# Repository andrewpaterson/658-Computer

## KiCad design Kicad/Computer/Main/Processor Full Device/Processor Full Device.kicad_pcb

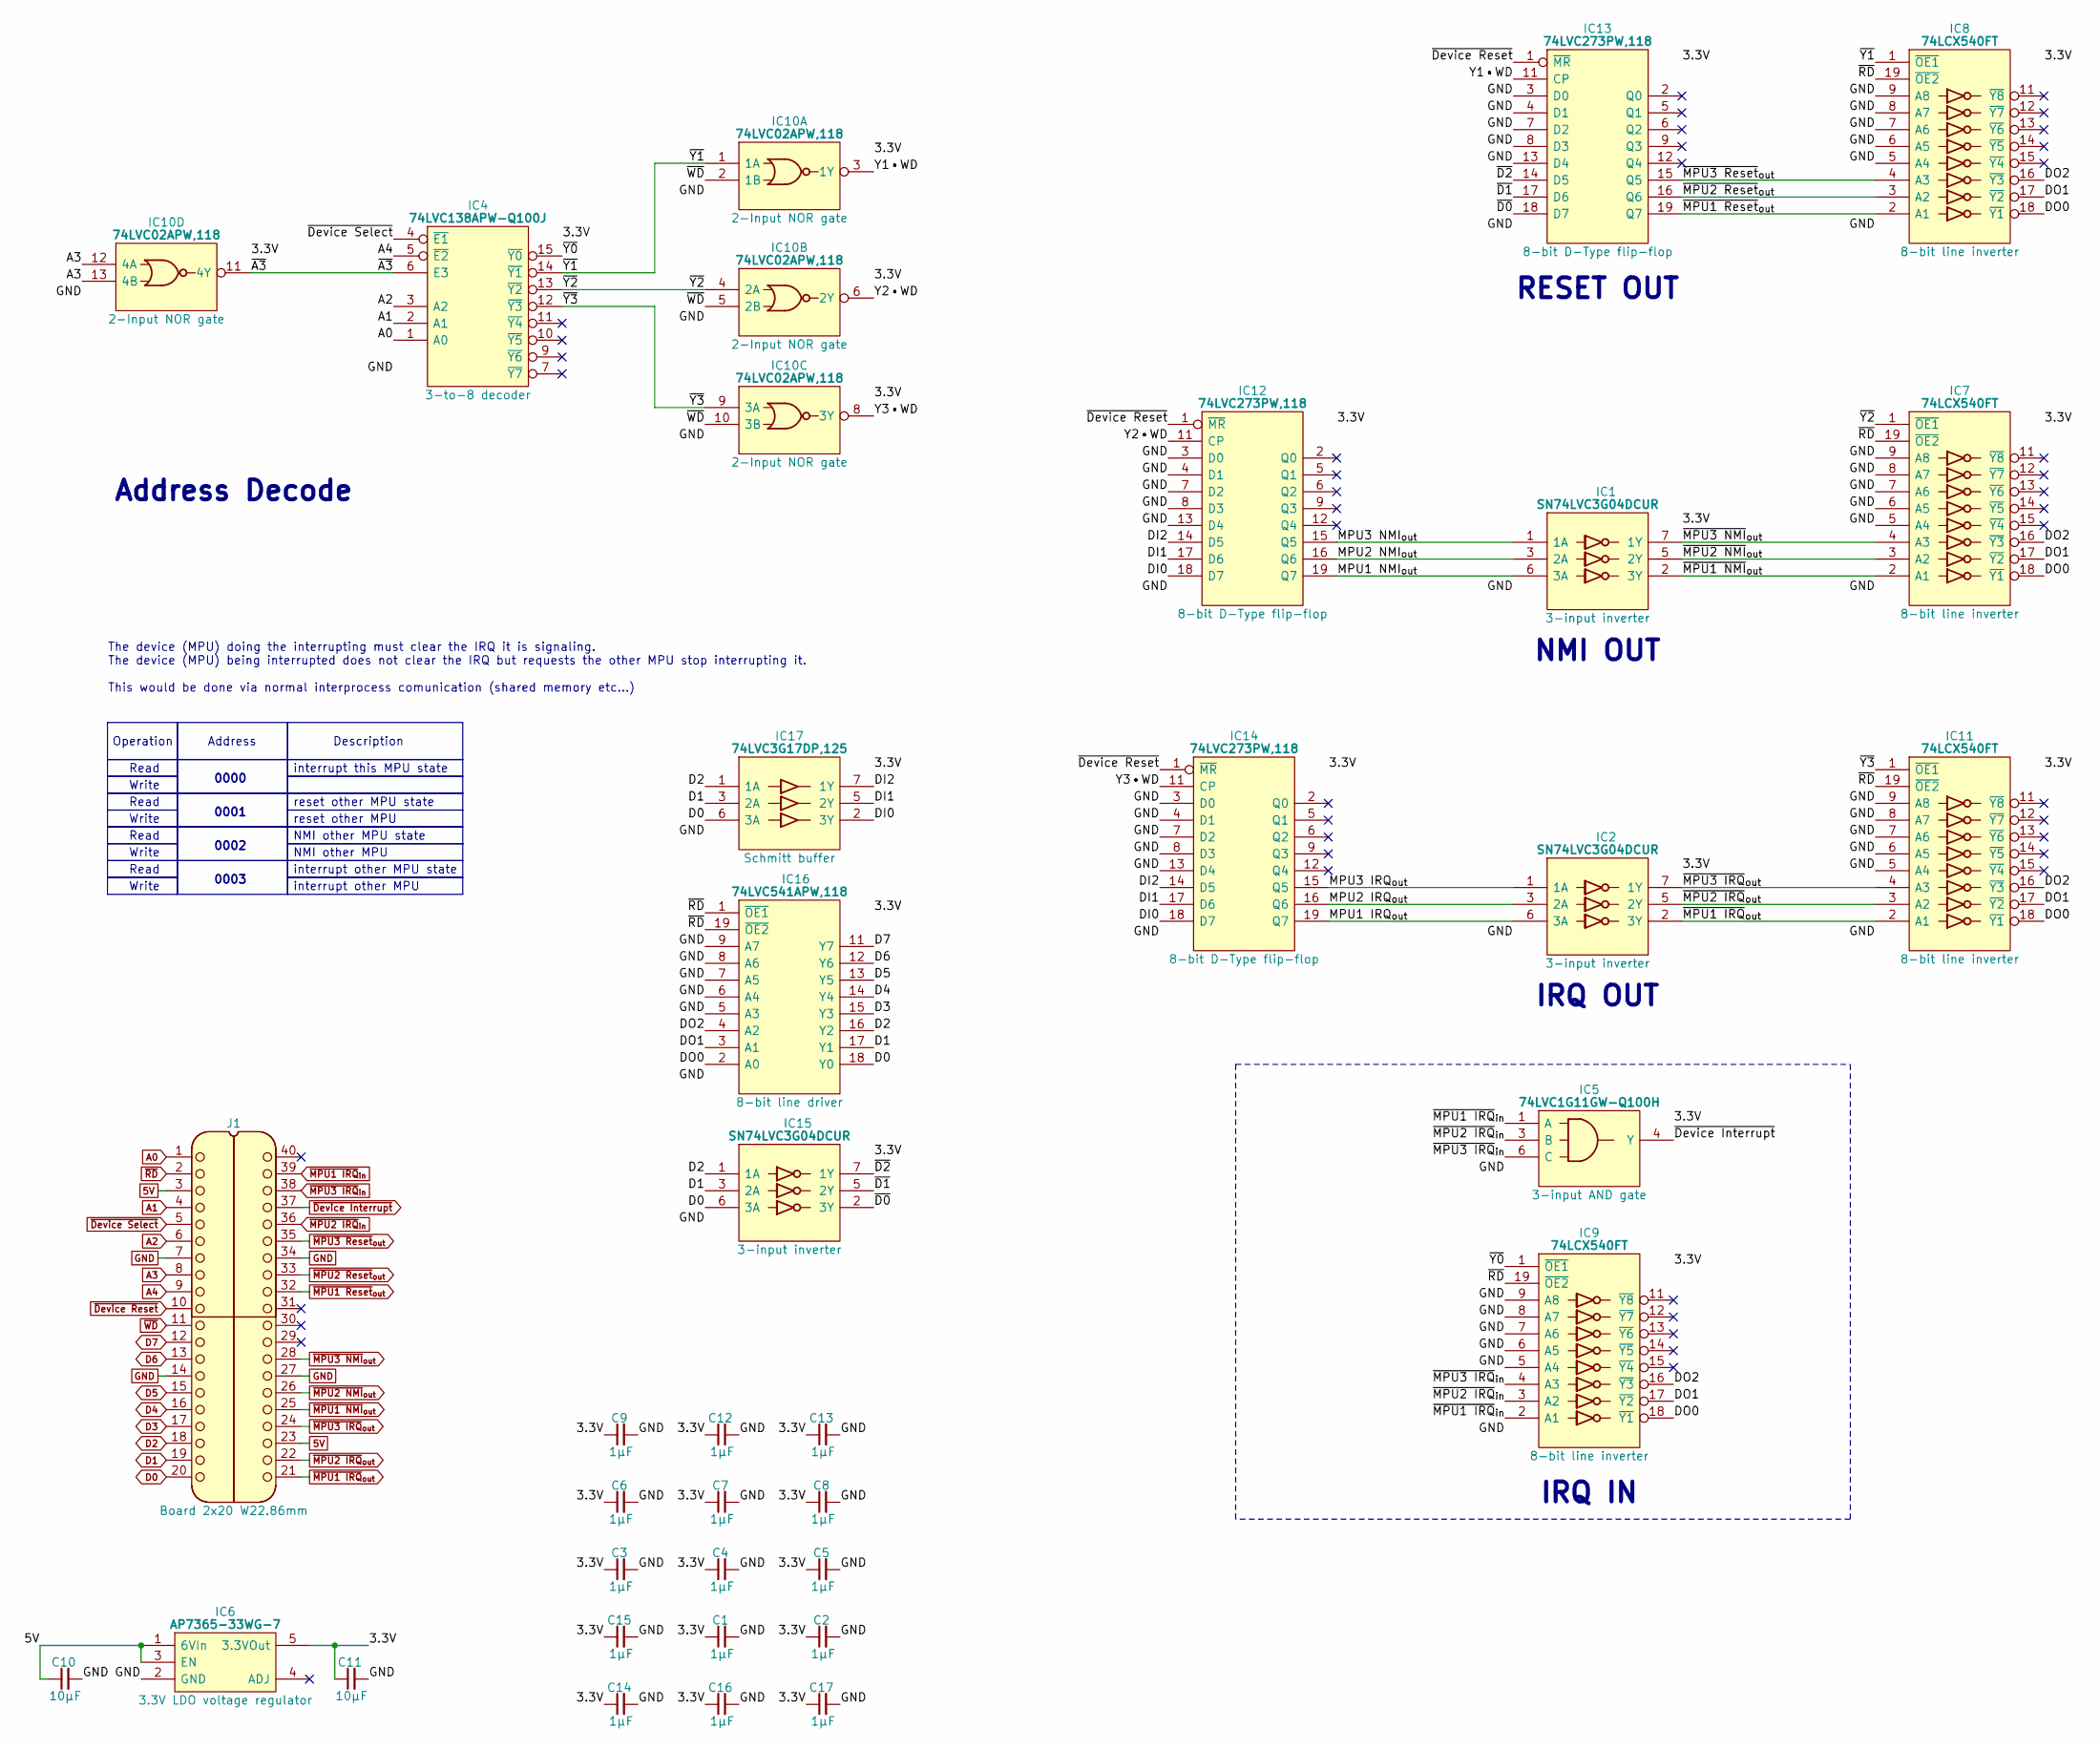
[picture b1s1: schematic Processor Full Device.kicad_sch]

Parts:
C1, C2, C3, C4, C5, C6, C7, C8, C9, C12, C13, C14, C15, C16, C17: 1μF; C_0805
C10, C11: 10µF; C_0805
IC1, IC2, IC15: SN74LVC3G04DCUR; SOP50P310X90-8N; Manufacturer_Part_Number SN74LVC3G04DCUR; Mouser Part Number 595-SN74LVC3G04DCUR
IC4: 74LVC138APW-Q100J; SOP65P640X110-16N; Mouser Part Number 771-74LVC138APWQ100J
IC5: 74LVC1G11GW-Q100H; SOP65P210X110-6N; Manufacturer_Part_Number 74LVC1G11GW-Q100H; Mouser Part Number 771-74LVC1G11GWQ100H
IC6: AP7365-33WG-7; SOT95P285X130-5N; Manufacturer_Part_Number AP7365-33WG-7; Mouser Part Number 621-AP7365-33WG-7
IC7, IC8, IC9, IC11: 74LCX540FT; SOP65P640X120-20N; Manufacturer_Part_Number 74LCX540FT; Mouser Part Number 757-74LCX540FT
IC10: 74LVC02APW,118; SOP65P640X110-14N; Mouser Part Number 771-74LVC02APW-T
IC12, IC13, IC14: 74LVC273PW,118; SOP65P640X110-20N; Manufacturer_Part_Number 74LVC273PW,118; Mouser Part Number 771-74LVC273PW-T
IC16: 74LVC541APW,118; SOP65P640X110-20N; Mouser Part Number 771-74LVC541APW-T
IC17: 74LVC3G17DP,125; SOP65P400X110-8N; Manufacturer_Part_Number 74LVC3G17DP,125; Mouser Part Number 771-LVC3G17DP125
J1: Board 2x20 W22.86mm; DIP-40_Board_W22.86mm

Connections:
5V: C10.1, IC6.1 (6VIn), IC6.3 (EN), J1.3, J1.23
/3.3V: C1.1, C2.1, C3.1, C4.1, C5.1, C6.1, C7.1, C8.1, C9.1, C11.1, C12.1, C13.1, C14.1, C15.1, C16.1, C17.1, IC1.8 (3V), IC2.8 (3V), IC4.16 (3V), IC5.5 (3V), IC6.5 (3.3VOut), IC7.20 (3V), IC8.20 (3V), IC9.20 (3V), IC10.14 (3V), IC11.20 (3V), IC12.20 (3V), IC13.20 (3V), IC14.20 (3V), IC15.8 (3V), IC16.20 (3V), IC17.8 (3V)
/DI0: IC12.18 (D7), IC14.18 (D7), IC17.2 (3Y)
/DI1: IC12.17 (D6), IC14.17 (D6), IC17.5 (2Y)
/DI2: IC12.14 (D5), IC14.14 (D5), IC17.7 (1Y)
/DO0: IC7.18 (~Y1), IC8.18 (~Y1), IC9.18 (~Y1), IC11.18 (~Y1), IC16.2 (A0)
/DO1: IC7.17 (~Y2), IC8.17 (~Y2), IC9.17 (~Y2), IC11.17 (~Y2), IC16.3 (A1)
/DO2: IC7.16 (~Y3), IC8.16 (~Y3), IC9.16 (~Y3), IC11.16 (~Y3), IC16.4 (A2)
/MPU1 IRQ_{out}: IC2.6 (3A), IC14.19 (Q7)
/MPU1 NMI_{out}: IC1.6 (3A), IC12.19 (Q7)
/MPU2 IRQ_{out}: IC2.3 (2A), IC14.16 (Q6)
/MPU2 NMI_{out}: IC1.3 (2A), IC12.16 (Q6)
/MPU3 IRQ_{out}: IC2.1 (1A), IC14.15 (Q5)
/MPU3 NMI_{out}: IC1.1 (1A), IC12.15 (Q5)
/Y1•WD: IC10.3 (1Y), IC13.11 (CP)
/Y2•WD: IC10.6 (2Y), IC12.11 (CP)
/Y3•WD: IC10.8 (3Y), IC14.11 (CP)
/~A3: IC4.6 (E3), IC10.11 (4Y)
/~D0: IC13.18 (D7), IC15.2 (3Y)
/~D1: IC13.17 (D6), IC15.5 (2Y)
/~D2: IC13.14 (D5), IC15.7 (1Y)
/~Y0: IC4.15 (~Y0), IC9.1 (~OE1)
/~Y1: IC4.14 (~Y1), IC8.1 (~OE1), IC10.1 (1A)
/~Y2: IC4.13 (~Y2), IC7.1 (~OE1), IC10.4 (2A)
/~Y3: IC4.12 (~Y3), IC10.9 (3A), IC11.1 (~OE1)
A0: IC4.1 (A0), J1.1
A1: IC4.2 (A1), J1.4
A2: IC4.3 (A2), J1.6
A3: IC10.12 (4A), IC10.13 (4B), J1.8
A4: IC4.5 (~E2), J1.9
D0: IC15.6 (3A), IC16.18 (Y0), IC17.6 (3A), J1.20
D1: IC15.3 (2A), IC16.17 (Y1), IC17.3 (2A), J1.19
D2: IC15.1 (1A), IC16.16 (Y2), IC17.1 (1A), J1.18
D3: IC16.15 (Y3), J1.17
D4: IC16.14 (Y4), J1.16
D5: IC16.13 (Y5), J1.15
D6: IC16.12 (Y6), J1.13
D7: IC16.11 (Y7), J1.12
GND: C1.2, C2.2, C3.2, C4.2, C5.2, C6.2, C7.2, C8.2, C9.2, C10.2, C11.2, C12.2, C13.2, C14.2, C15.2, C16.2, C17.2, IC1.4 (GND), IC2.4 (GND), IC4.8 (GND), IC5.2 (GND), IC6.2 (GND), IC7.5 (A4), IC7.6 (A5), IC7.7 (A6), IC7.8 (A7), IC7.9 (A8), IC7.10 (GND), IC8.5 (A4), IC8.6 (A5), IC8.7 (A6), IC8.8 (A7), IC8.9 (A8), IC8.10 (GND), IC9.5 (A4), IC9.6 (A5), IC9.7 (A6), IC9.8 (A7), IC9.9 (A8), IC9.10 (GND), IC10.7 (GND), IC11.5 (A4), IC11.6 (A5), IC11.7 (A6), IC11.8 (A7), IC11.9 (A8), IC11.10 (GND), IC12.3 (D0), IC12.4 (D1), IC12.7 (D2), IC12.8 (D3), IC12.10 (GND), IC12.13 (D4), IC13.3 (D0), IC13.4 (D1), IC13.7 (D2), IC13.8 (D3), IC13.10 (GND), IC13.13 (D4), IC14.3 (D0), IC14.4 (D1), IC14.7 (D2), IC14.8 (D3), IC14.10 (GND), IC14.13 (D4), IC15.4 (GND), IC16.5 (A3), IC16.6 (A4), IC16.7 (A5), IC16.8 (A6), IC16.9 (A7), IC16.10 (GND), IC17.4 (GND), J1.7, J1.14, J1.27, J1.34
~Device Interrupt: IC5.4 (Y), J1.37
~Device Reset: IC12.1 (~MR), IC13.1 (~MR), IC14.1 (~MR), J1.10
~Device Select: IC4.4 (~E1), J1.5
~MPU1 IRQ_{in}: IC5.1 (A), IC9.2 (A1), J1.39
~MPU1 IRQ_{out}: IC2.2 (3Y), IC11.2 (A1), J1.21
~MPU1 NMI_{out}: IC1.2 (3Y), IC7.2 (A1), J1.25
~MPU1 Reset_{out}: IC8.2 (A1), IC13.19 (Q7), J1.32
~MPU2 IRQ_{in}: IC5.3 (B), IC9.3 (A2), J1.36
~MPU2 IRQ_{out}: IC2.5 (2Y), IC11.3 (A2), J1.22
~MPU2 NMI_{out}: IC1.5 (2Y), IC7.3 (A2), J1.26
~MPU2 Reset_{out}: IC8.3 (A2), IC13.16 (Q6), J1.33
~MPU3 IRQ_{in}: IC5.6 (C), IC9.4 (A3), J1.38
~MPU3 IRQ_{out}: IC2.7 (1Y), IC11.4 (A3), J1.24
~MPU3 NMI_{out}: IC1.7 (1Y), IC7.4 (A3), J1.28
~MPU3 Reset_{out}: IC8.4 (A3), IC13.15 (Q5), J1.35
~RD: IC7.19 (~OE2), IC8.19 (~OE2), IC9.19 (~OE2), IC11.19 (~OE2), IC16.1 (~OE1), IC16.19 (~OE2), J1.2
~WD: IC10.2 (1B), IC10.5 (2B), IC10.10 (3B), J1.11

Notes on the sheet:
interrupt other MPU
Operation
Read
Address Decode
0001
Write
reset other MPU
NMI other MPU state
interrupt this MPU state
IRQ IN
Address
The device (MPU) doing the interrupting must clear the IRQ it is signaling. The device (MPU) being interrupted does not clear the IRQ but requests the other MPU stop interrupting it. This would be done via normal interprocess comunication (shared memory etc...)
NMI OUT
interrupt other MPU state
0003
NMI other MPU
RESET OUT
IRQ OUT
0000
0002
reset other MPU state
Description

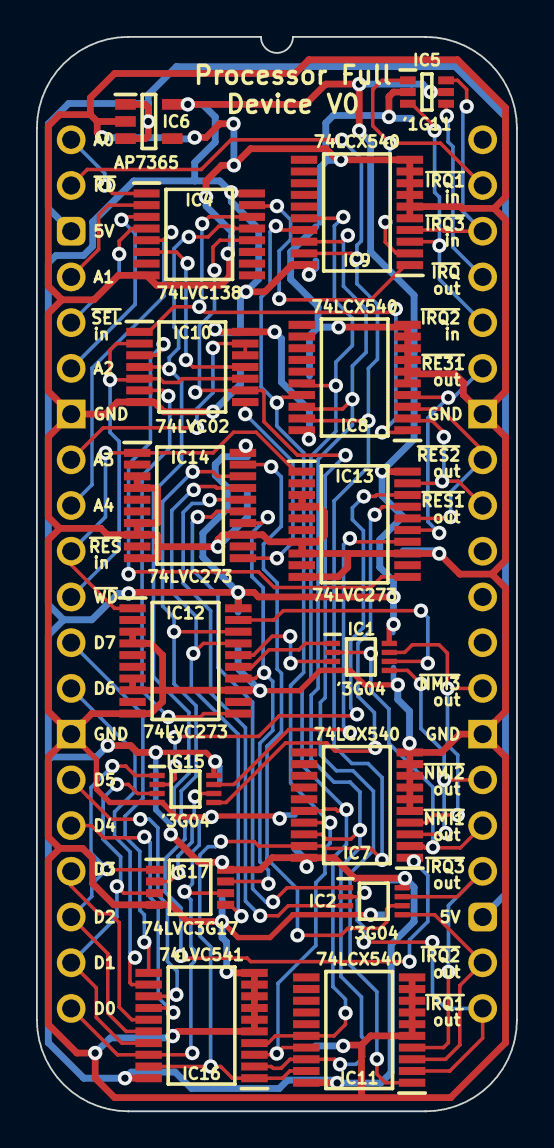
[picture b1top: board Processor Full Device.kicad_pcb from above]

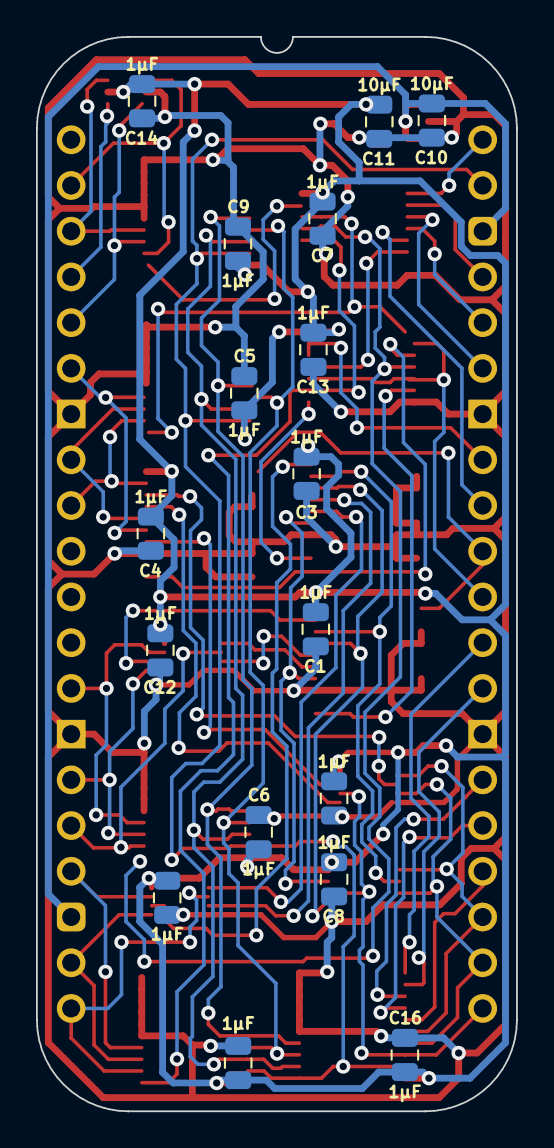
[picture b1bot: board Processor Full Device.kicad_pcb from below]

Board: 2 copper layers, 26.7 x 59.7 mm, 34 parts (17 on the bottom side), 56 nets.

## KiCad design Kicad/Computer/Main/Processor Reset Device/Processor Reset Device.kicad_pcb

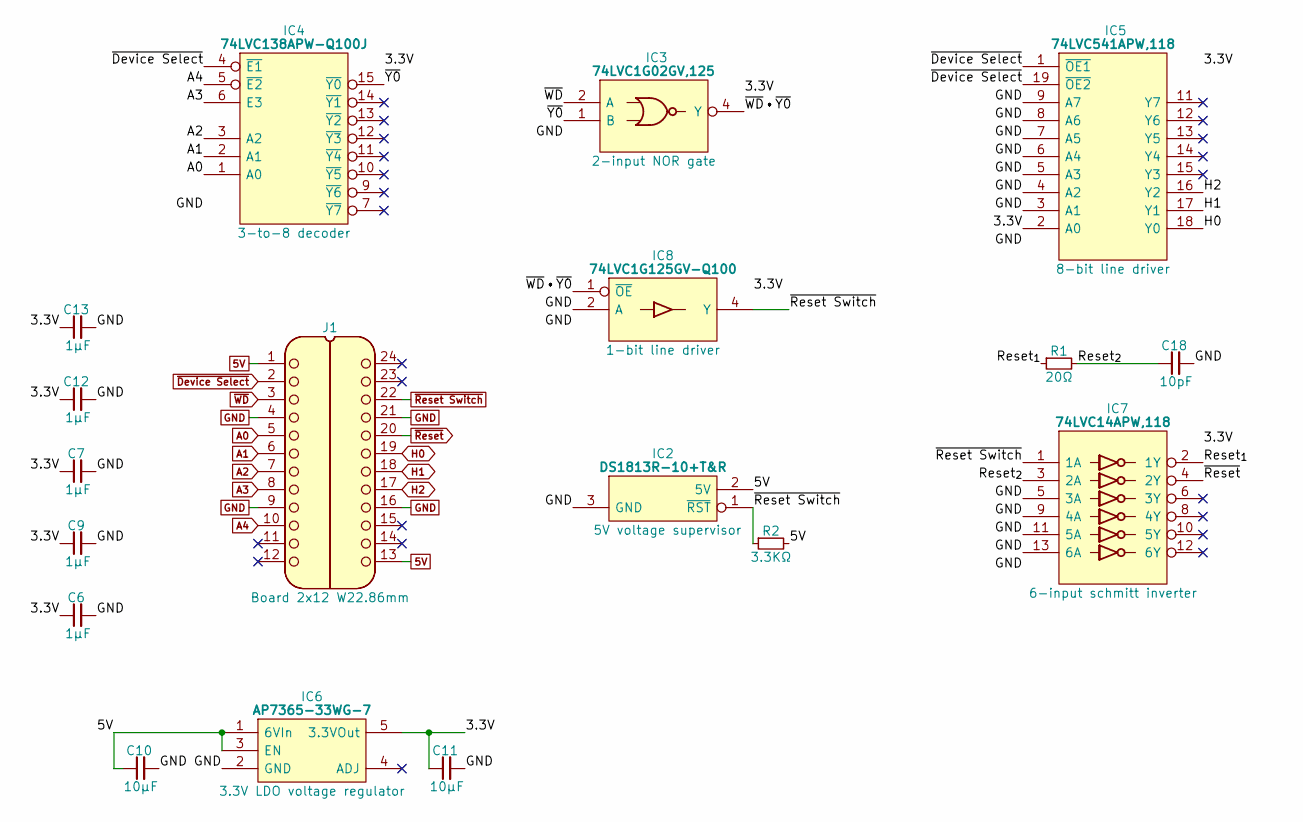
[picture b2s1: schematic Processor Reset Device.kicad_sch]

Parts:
C6, C7, C9, C12, C13: 1μF; C_0805
C10, C11: 10µF; C_0805
C18: 10pF; C_0805
IC2: DS1813R-10+T&R; SOT95P237X112-3N; Mouser Part Number 700-DS1813R-10T&R
IC3: 74LVC1G02GV,125; SOT95P275X110-5N; Manufacturer_Part_Number 74LVC1G02GV,125; Mouser Part Number 771-LVC1G02GV125
IC4: 74LVC138APW-Q100J; SOP65P640X110-16N; Mouser Part Number 771-74LVC138APWQ100J
IC5: 74LVC541APW,118; SOP65P640X110-20N; Mouser Part Number 771-74LVC541APW-T
IC6: AP7365-33WG-7; SOT95P285X130-5N; Manufacturer_Part_Number AP7365-33WG-7; Mouser Part Number 621-AP7365-33WG-7
IC7: 74LVC14APW,118; SOP65P640X110-14N; Manufacturer_Part_Number 74LVC14APW,118; Mouser Part Number 771-74LVC14APW-T
IC8: 74LVC1G125GV-Q100; SOT95P275X110-5N; Mouser Part Number 771-74LVC1G125GVQ100
J1: Board 2x12 W22.86mm; DIP-24_Board_W22.86mm
J4: Pin_Header_01x12; PinHeader_1x12_P2.54mm_Vertical
R1: 20Ω; R_0805
R2: 3.3KΩ; R_0805

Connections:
5V: C10.1, IC2.2 (5V), IC6.1 (6VIn), IC6.3 (EN), J1.1, J1.13, R2.2
/3.3V: C6.1, C7.1, C9.1, C11.1, C12.1, C13.1, IC3.5 (3V), IC4.16 (3V), IC5.2 (A0), IC5.20 (3V), IC6.5 (3.3VOut), IC7.14 (3V), IC8.5 (3V)
/Reset_{1}: IC7.2 (1Y), R1.1
/Reset_{2}: C18.1, IC7.3 (2A), R1.2
/~WD•~Y0: IC3.4 (Y), IC8.1 (~OE)
/~Y0: IC3.1 (B), IC4.15 (~Y0)
A0: IC4.1 (A0), J1.5
A1: IC4.2 (A1), J1.6
A2: IC4.3 (A2), J1.7
A3: IC4.6 (E3), J1.8
A4: IC4.5 (~E2), J1.10
GND: C6.2, C7.2, C9.2, C10.2, C11.2, C12.2, C13.2, C18.2, IC2.3 (GND), IC3.3 (GND), IC4.8 (GND), IC5.3 (A1), IC5.4 (A2), IC5.5 (A3), IC5.6 (A4), IC5.7 (A5), IC5.8 (A6), IC5.9 (A7), IC5.10 (GND), IC6.2 (GND), IC7.5 (3A), IC7.7 (GND), IC7.9 (4A), IC7.11 (5A), IC7.13 (6A), IC8.2 (A), IC8.3 (GND), J1.4, J1.9, J1.16, J1.21
H0: IC5.18 (Y0), J1.19
H1: IC5.17 (Y1), J1.18
H2: IC5.16 (Y2), J1.17
~Device Select: IC4.4 (~E1), IC5.1 (~OE1), IC5.19 (~OE2), J1.2
~Reset Switch: IC2.1 (~RST), IC7.1 (1A), IC8.4 (Y), J1.22, R2.1
~Reset: IC7.4 (2Y), J1.20
~WD: IC3.2 (A), J1.3

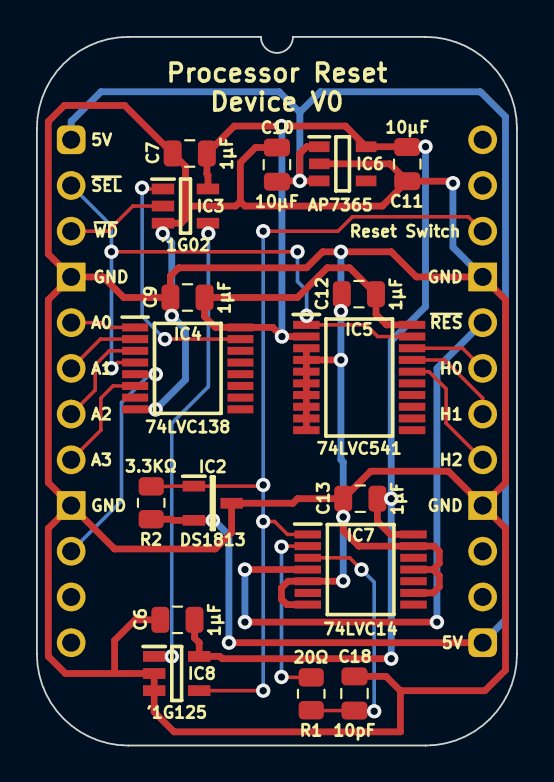
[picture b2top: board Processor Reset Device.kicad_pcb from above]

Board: 2 copper layers, 26.7 x 39.4 mm, 19 parts (1 on the bottom side), 19 nets.

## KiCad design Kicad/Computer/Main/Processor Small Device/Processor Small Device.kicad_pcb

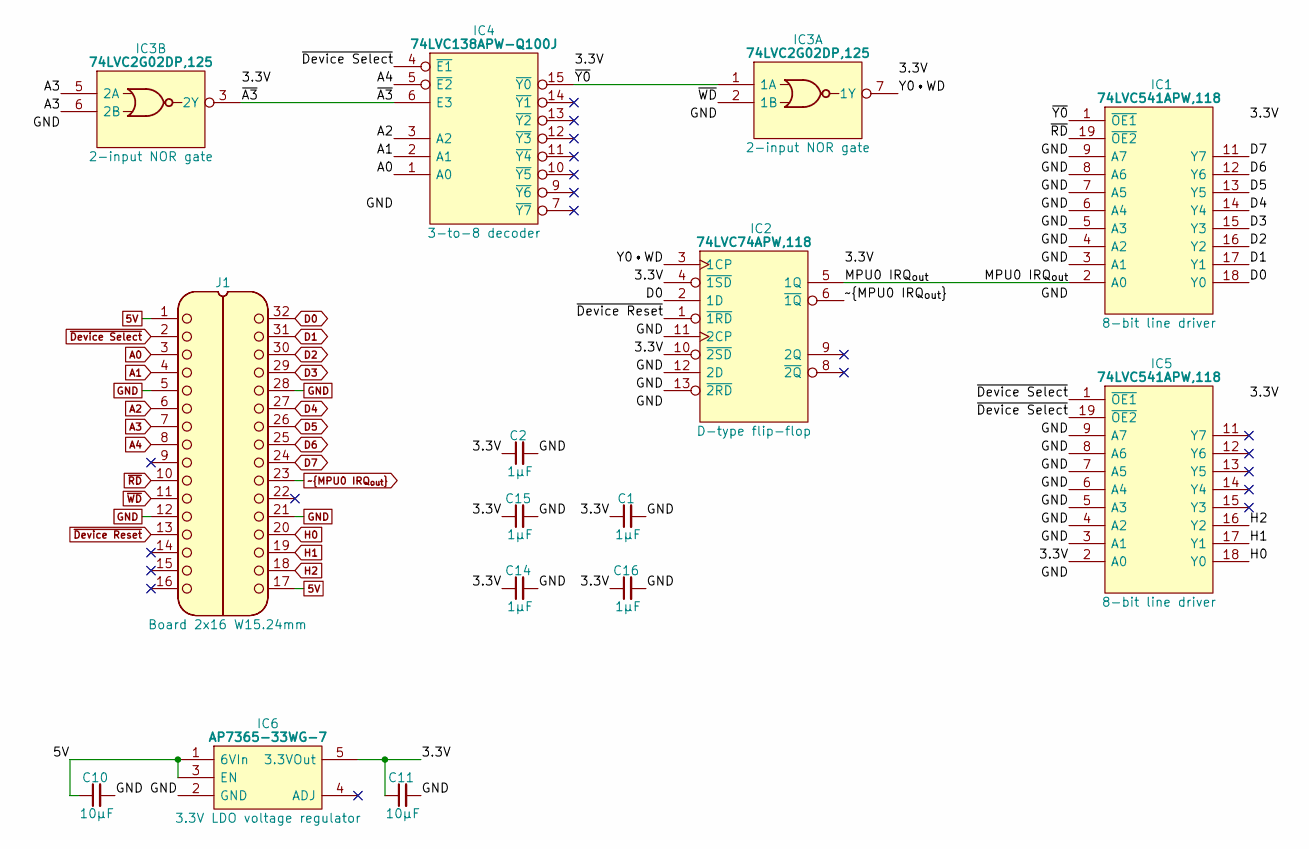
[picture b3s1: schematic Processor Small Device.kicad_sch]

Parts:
C1, C2, C14, C15, C16: 1μF; C_0805
C10, C11: 10µF; C_0805
IC1, IC5: 74LVC541APW,118; SOP65P640X110-20N; Mouser Part Number 771-74LVC541APW-T
IC2: 74LVC74APW,118; SOP65P640X110-14N; Mouser Part Number 771-74LVC74APW-T
IC3: 74LVC2G02DP,125; SOP65P400X110-8N; Mouser Part Number 771-LVC2G02DP125
IC4: 74LVC138APW-Q100J; SOP65P640X110-16N; Mouser Part Number 771-74LVC138APWQ100J
IC6: AP7365-33WG-7; SOT95P285X130-5N; Manufacturer_Part_Number AP7365-33WG-7; Mouser Part Number 621-AP7365-33WG-7
J1: Board 2x16 W15.24mm; DIP-32_Board_W15.24mm

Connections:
5V: C10.1, IC6.1 (6VIn), IC6.3 (EN), J1.1, J1.17
/3.3V: C1.1, C2.1, C11.1, C14.1, C15.1, C16.1, IC1.20 (3V), IC2.4 (~1SD), IC2.10 (~2SD), IC2.14 (3V), IC3.8 (3V), IC4.16 (3V), IC5.2 (A0), IC5.20 (3V), IC6.5 (3.3VOut)
/MPU0 IRQ_{out}: IC1.2 (A0), IC2.5 (1Q)
/Y0•WD: IC2.3 (1CP), IC3.7 (1Y)
/~A3: IC3.3 (2Y), IC4.6 (E3)
/~Y0: IC1.1 (~OE1), IC3.1 (1A), IC4.15 (~Y0)
A0: IC4.1 (A0), J1.3
A1: IC4.2 (A1), J1.4
A2: IC4.3 (A2), J1.6
A3: IC3.5 (2A), IC3.6 (2B), J1.7
A4: IC4.5 (~E2), J1.8
D0: IC1.18 (Y0), IC2.2 (1D), J1.32
D1: IC1.17 (Y1), J1.31
D2: IC1.16 (Y2), J1.30
D3: IC1.15 (Y3), J1.29
D4: IC1.14 (Y4), J1.27
D5: IC1.13 (Y5), J1.26
D6: IC1.12 (Y6), J1.25
D7: IC1.11 (Y7), J1.24
GND: C1.2, C2.2, C10.2, C11.2, C14.2, C15.2, C16.2, IC1.3 (A1), IC1.4 (A2), IC1.5 (A3), IC1.6 (A4), IC1.7 (A5), IC1.8 (A6), IC1.9 (A7), IC1.10 (GND), IC2.7 (GND), IC2.11 (2CP), IC2.12 (2D), IC2.13 (~2RD), IC3.4 (GND), IC4.8 (GND), IC5.3 (A1), IC5.4 (A2), IC5.5 (A3), IC5.6 (A4), IC5.7 (A5), IC5.8 (A6), IC5.9 (A7), IC5.10 (GND), IC6.2 (GND), J1.5, J1.12, J1.21, J1.28
H0: IC5.18 (Y0), J1.20
H1: IC5.17 (Y1), J1.19
H2: IC5.16 (Y2), J1.18
~Device Reset: IC2.1 (~1RD), J1.13
~Device Select: IC4.4 (~E1), IC5.1 (~OE1), IC5.19 (~OE2), J1.2
~MPU0 IRQ_{out}: IC2.6 (~1Q), J1.23
~RD: IC1.19 (~OE2), J1.10
~WD: IC3.2 (1B), J1.11

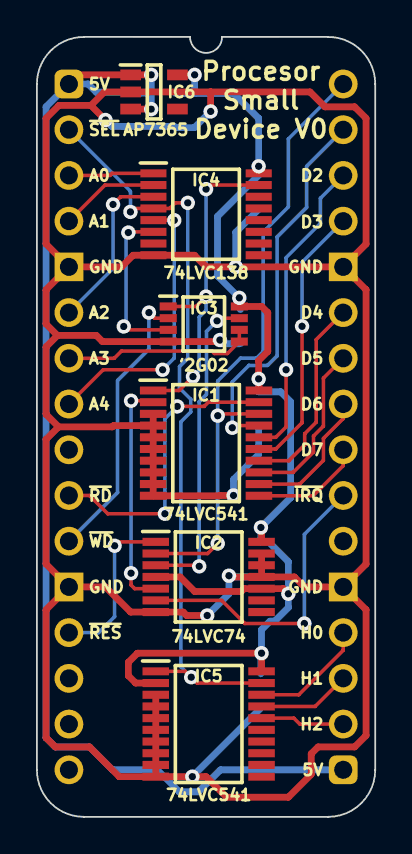
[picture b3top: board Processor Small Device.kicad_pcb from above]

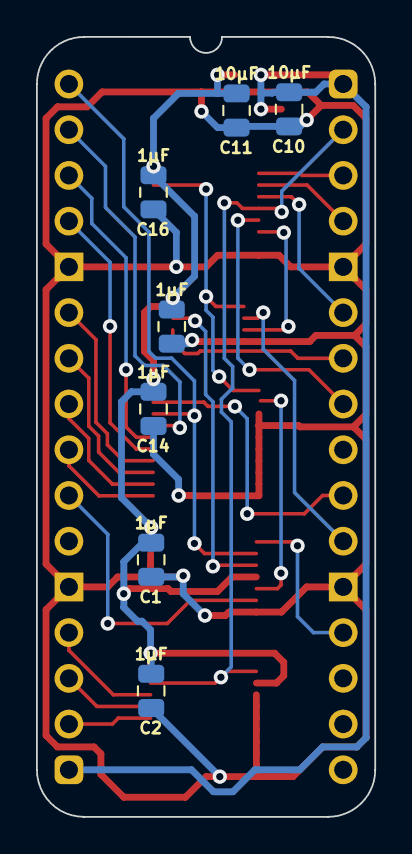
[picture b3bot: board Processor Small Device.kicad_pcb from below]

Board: 2 copper layers, 18.8 x 43.3 mm, 14 parts (7 on the bottom side), 28 nets.

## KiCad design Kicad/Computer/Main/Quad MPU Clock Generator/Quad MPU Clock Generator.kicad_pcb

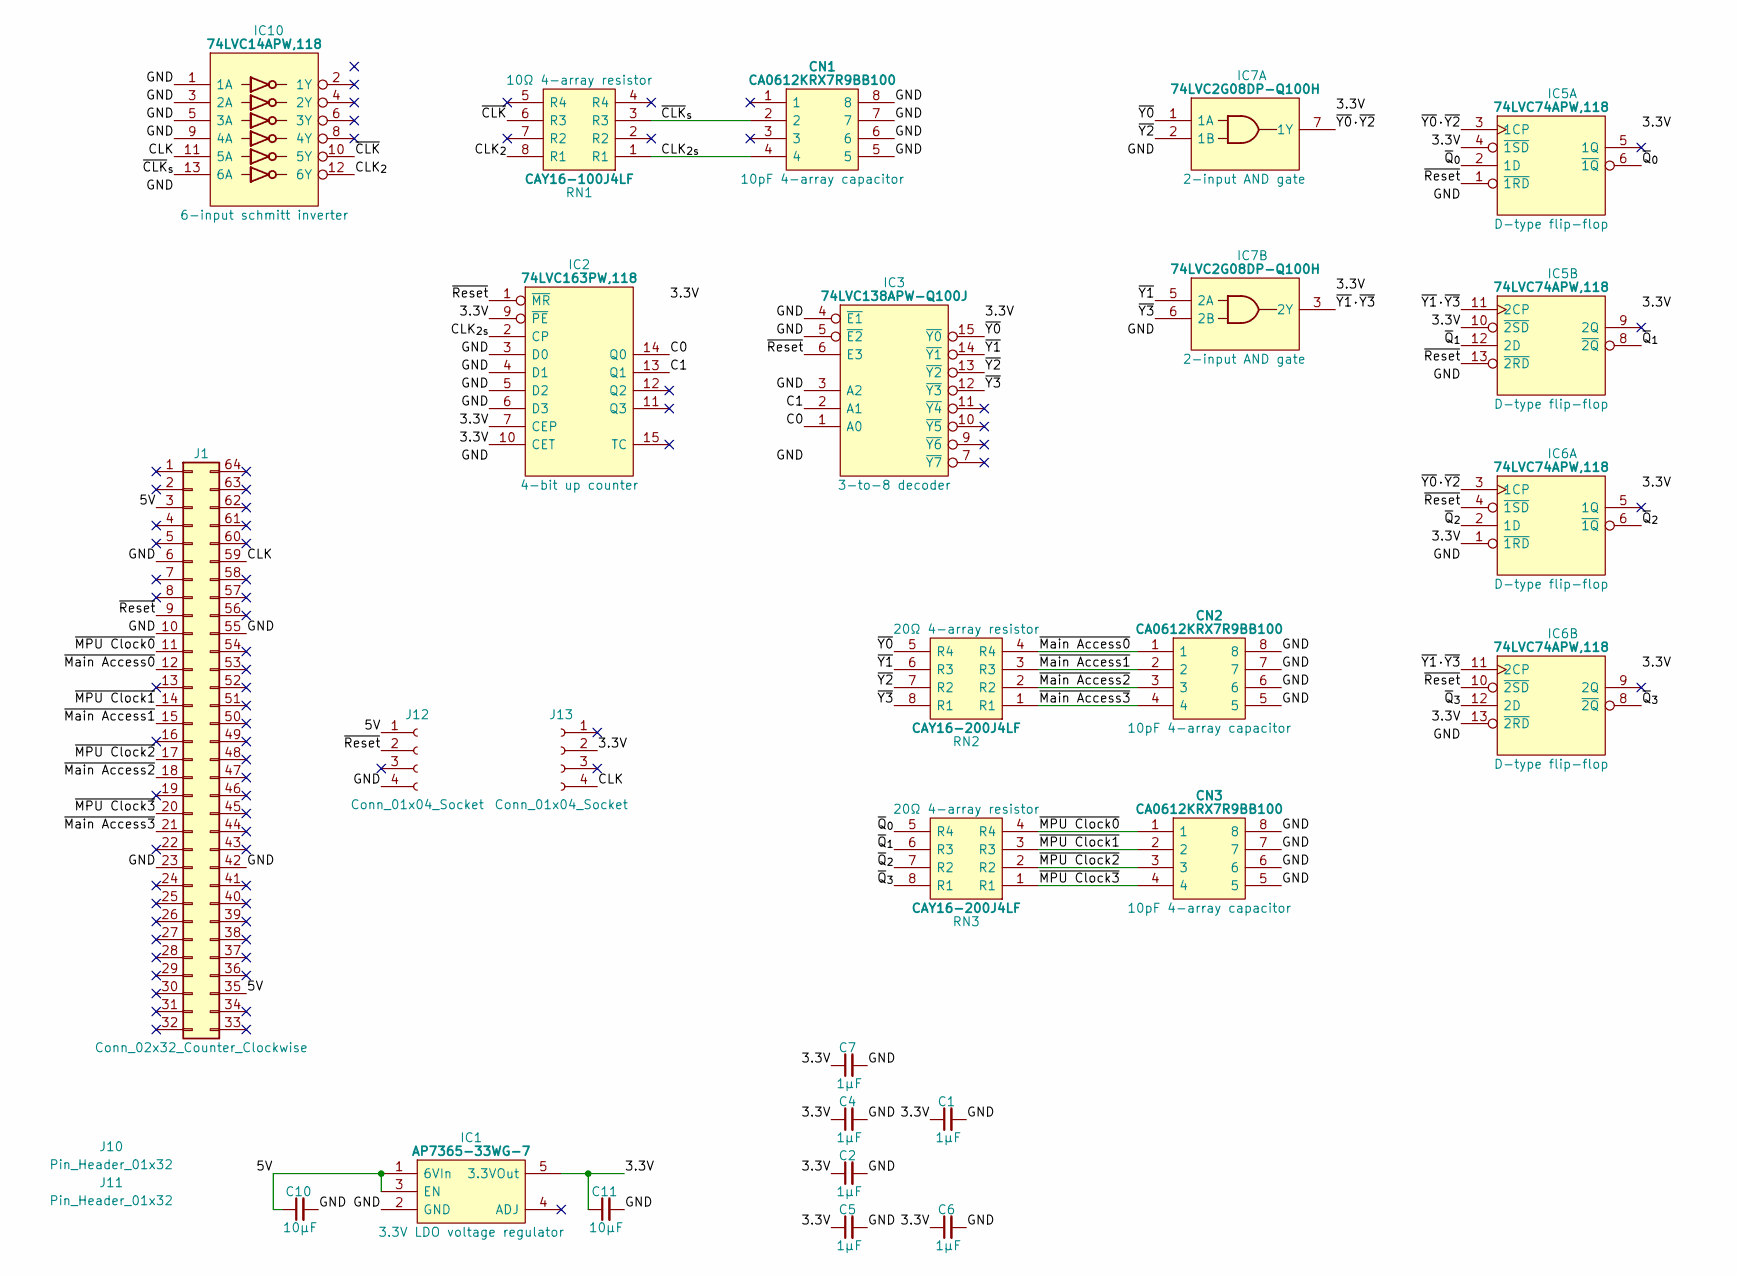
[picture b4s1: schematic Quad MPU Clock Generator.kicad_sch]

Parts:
C1, C2, C4, C5, C6, C7: 1μF; C_0805
C10, C11: 10µF; C_0805
CN1, CN2, CN3: CA0612KRX7R9BB100; Manufacturer_Part_Number CA0612KRX7R9BB102; Mouser Part Number 603-CA612KRX7R9BB102
IC1: AP7365-33WG-7; SOT95P285X130-5N; Manufacturer_Part_Number AP7365-33WG-7; Mouser Part Number 621-AP7365-33WG-7
IC2: 74LVC163PW,118; SOP65P640X110-16N; Mouser Part Number 771-74LVC163PW-T
IC3: 74LVC138APW-Q100J; SOP65P640X110-16N; Mouser Part Number 771-74LVC138APWQ100J
IC5, IC6: 74LVC74APW,118; SOP65P640X110-14N; Mouser Part Number 771-74LVC74APW-T
IC7: 74LVC2G08DP-Q100H; SOP65P400X110-8N; Manufacturer_Part_Number 74LVC2G08DP-Q100H; Mouser Part Number 771-74LVC2G08DPQ100H
IC10: 74LVC14APW,118; SOP65P640X110-14N; Manufacturer_Part_Number 74LVC14APW,118; Mouser Part Number 771-74LVC14APW-T
J1: Conn_02x32_Counter_Clockwise; DIP-64_Board_W22.86mm
J10, J11: Pin_Header_01x32; PinHeader_1x32_P2.54mm_Vertical
J12, J13: Conn_01x04_Socket; PinSocket_1x04_P2.54mm_Vertical
RN1: CAY16-100J4LF; CAY16-F4; Manufacturer_Part_Number CAY16-331J4LF; Mouser Part Number 652-CAY16-331J4LF
RN2, RN3: CAY16-200J4LF; CAY16-F4; Manufacturer_Part_Number CAY16-331J4LF; Mouser Part Number 652-CAY16-331J4LF

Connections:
/3.3V: C1.1, C2.1, C4.1, C5.1, C6.1, C7.1, C11.1, IC1.5 (3.3VOut), IC2.7 (CEP), IC2.9 (~PE), IC2.10 (CET), IC2.16 (3V), IC3.16 (3V), IC5.4 (~1SD), IC5.10 (~2SD), IC5.14 (3V), IC6.1 (~1RD), IC6.13 (~2RD), IC6.14 (3V), IC7.8 (3V), J13.2
/5V: C10.1, IC1.1 (6VIn), IC1.3 (EN), J1.3, J1.35, J12.1
/C0: IC2.14 (Q0), IC3.1 (A0)
/C1: IC2.13 (Q1), IC3.2 (A1)
/CLK: IC10.11 (5A), J1.59, J13.4
/CLK_{2s}: CN1.4, IC2.2 (CP), RN1.1 (R1)
/CLK_{2}: IC10.12 (6Y), RN1.8 (R1)
/GND: C1.2, C2.2, C4.2, C5.2, C6.2, C7.2, C10.2, C11.2, CN1.5, CN1.6, CN1.7, CN1.8, CN2.5, CN2.6, CN2.7, CN2.8, CN3.5, CN3.6, CN3.7, CN3.8, IC1.2 (GND), IC2.3 (D0), IC2.4 (D1), IC2.5 (D2), IC2.6 (D3), IC2.8 (GND), IC3.3 (A2), IC3.4 (~E1), IC3.5 (~E2), IC3.8 (GND), IC5.7 (GND), IC6.7 (GND), IC7.4 (GND), IC10.1 (1A), IC10.3 (2A), IC10.5 (3A), IC10.7 (GND), IC10.9 (4A), J1.6, J1.10, J1.23, J1.42, J1.55, J12.4
/~CLK: IC10.10 (5Y), RN1.6 (R3)
/~CLK_{s}: CN1.2, IC10.13 (6A), RN1.3 (R3)
/~MPU Clock0: CN3.1, J1.11, RN3.4 (R4)
/~MPU Clock1: CN3.2, J1.14, RN3.3 (R3)
/~MPU Clock2: CN3.3, J1.17, RN3.2 (R2)
/~MPU Clock3: CN3.4, J1.20, RN3.1 (R1)
/~Main Access0: CN2.1, J1.12, RN2.4 (R4)
/~Main Access1: CN2.2, J1.15, RN2.3 (R3)
/~Main Access2: CN2.3, J1.18, RN2.2 (R2)
/~Main Access3: CN2.4, J1.21, RN2.1 (R1)
/~Q_{0}: IC5.2 (1D), IC5.6 (~1Q), RN3.5 (R4)
/~Q_{1}: IC5.8 (~2Q), IC5.12 (2D), RN3.6 (R3)
/~Q_{2}: IC6.2 (1D), IC6.6 (~1Q), RN3.7 (R2)
/~Q_{3}: IC6.8 (~2Q), IC6.12 (2D), RN3.8 (R1)
/~Reset: IC2.1 (~MR), IC3.6 (E3), IC5.1 (~1RD), IC5.13 (~2RD), IC6.4 (~1SD), IC6.10 (~2SD), J1.9, J12.2
/~Y0: IC3.15 (~Y0), IC7.1 (1A), RN2.5 (R4)
/~Y0·~Y2: IC5.3 (1CP), IC6.3 (1CP), IC7.7 (1Y)
/~Y1: IC3.14 (~Y1), IC7.5 (2A), RN2.6 (R3)
/~Y1·~Y3: IC5.11 (2CP), IC6.11 (2CP), IC7.3 (2Y)
/~Y2: IC3.13 (~Y2), IC7.2 (1B), RN2.7 (R2)
/~Y3: IC3.12 (~Y3), IC7.6 (2B), RN2.8 (R1)

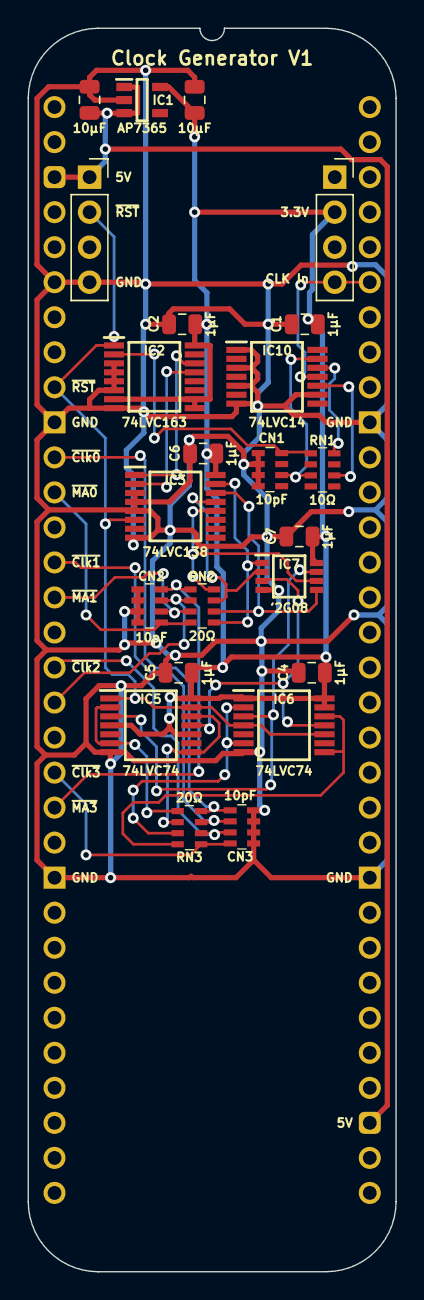
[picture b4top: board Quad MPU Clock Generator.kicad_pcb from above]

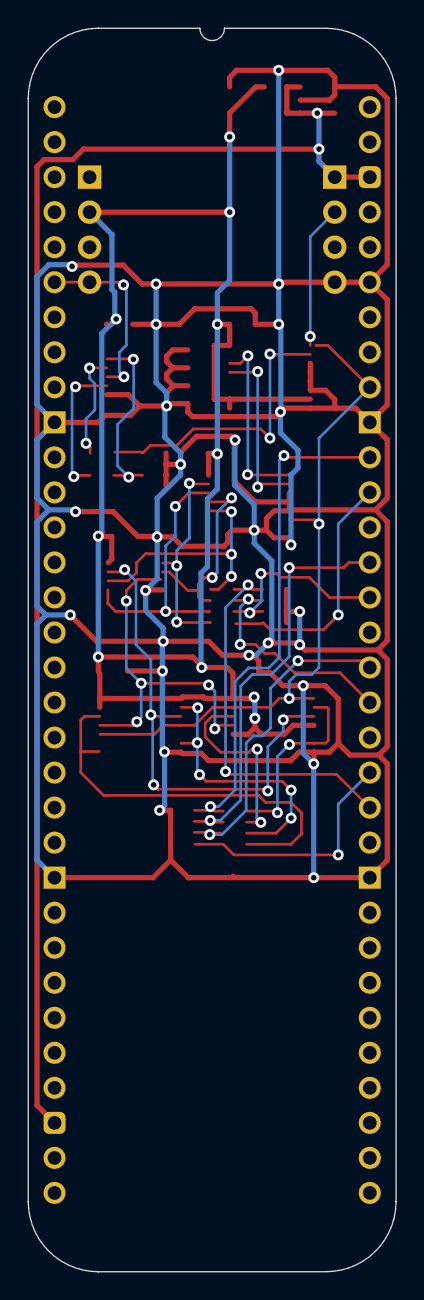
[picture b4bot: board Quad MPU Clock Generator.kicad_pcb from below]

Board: 2 copper layers, 26.7 x 90.2 mm, 26 parts (2 on the bottom side), 29 nets.
